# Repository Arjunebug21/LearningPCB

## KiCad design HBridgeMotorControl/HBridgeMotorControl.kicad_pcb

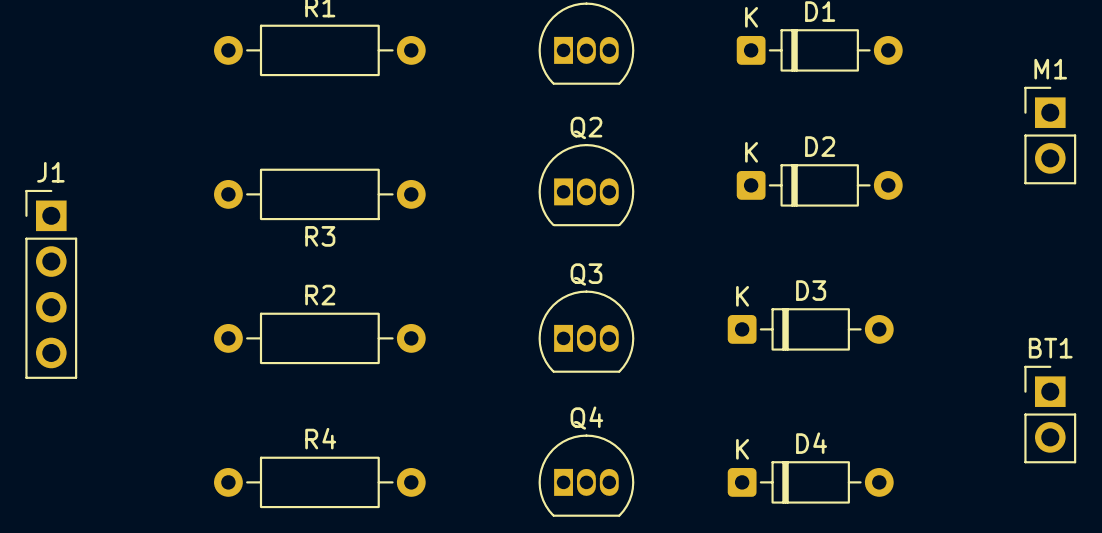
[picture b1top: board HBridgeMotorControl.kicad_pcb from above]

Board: 2 copper layers, 15 parts (0 on the bottom side), 12 nets, no tracks yet.

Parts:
BT1: 5V; PinHeader_1x02_P2.54mm_Vertical
D1, D2, D3, D4: 1N914; D_DO-35_SOD27_P7.62mm_Horizontal
J1: Conn_01x04; PinHeader_1x04_P2.54mm_Vertical
M1: Motor_DC; PinHeader_1x02_P2.54mm_Vertical
Q1, Q2: PNP; TO-92_Inline
Q3, Q4: NPN; TO-92_Inline
R1, R2, R3, R4: 850; R_Axial_DIN0207_L6.3mm_D2.5mm_P10.16mm_Horizontal

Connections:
GND: BT1.2 (-), D3.2 (A), D4.2 (A), Q3.3 (E), Q4.3 (E)
unnamed: BT1.1 (+), D1.1 (K), D2.1 (K), Q1.3 (E), Q2.3 (E)
unnamed: D1.2 (A), D3.1 (K), M1.1 (+), Q1.1 (C), Q3.1 (C)
unnamed: D2.2 (A), D4.1 (K), M1.2 (-), Q2.1 (C), Q4.1 (C)
unnamed: J1.1, R1.1
unnamed: J1.2, R2.1
unnamed: J1.3, R3.2
unnamed: J1.4, R4.2
unnamed: Q1.2 (B), R1.2
unnamed: Q2.2 (B), R3.1
unnamed: Q3.2 (B), R2.2
unnamed: Q4.2 (B), R4.1

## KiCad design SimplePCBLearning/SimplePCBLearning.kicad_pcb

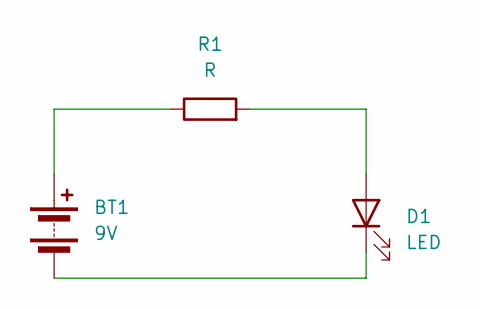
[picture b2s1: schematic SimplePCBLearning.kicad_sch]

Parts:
BT1: 9V; PinSocket_1x02_P2.54mm_Vertical
D1: LED; LED_D3.0mm
R1: R; R_Axial_DIN0207_L6.3mm_D2.5mm_P10.16mm_Horizontal

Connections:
unnamed: BT1.1 (+), R1.1
unnamed: BT1.2 (-), D1.1 (K)
unnamed: D1.2 (A), R1.2

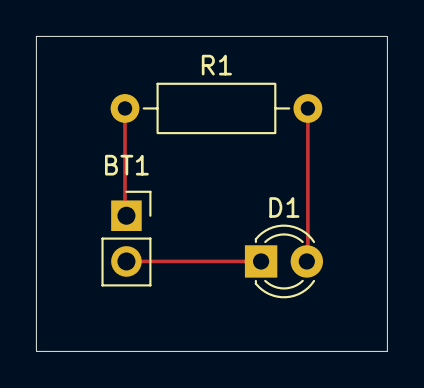
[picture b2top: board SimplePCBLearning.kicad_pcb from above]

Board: 2 copper layers, 19.5 x 17.5 mm, 3 parts (0 on the bottom side), 3 nets.
